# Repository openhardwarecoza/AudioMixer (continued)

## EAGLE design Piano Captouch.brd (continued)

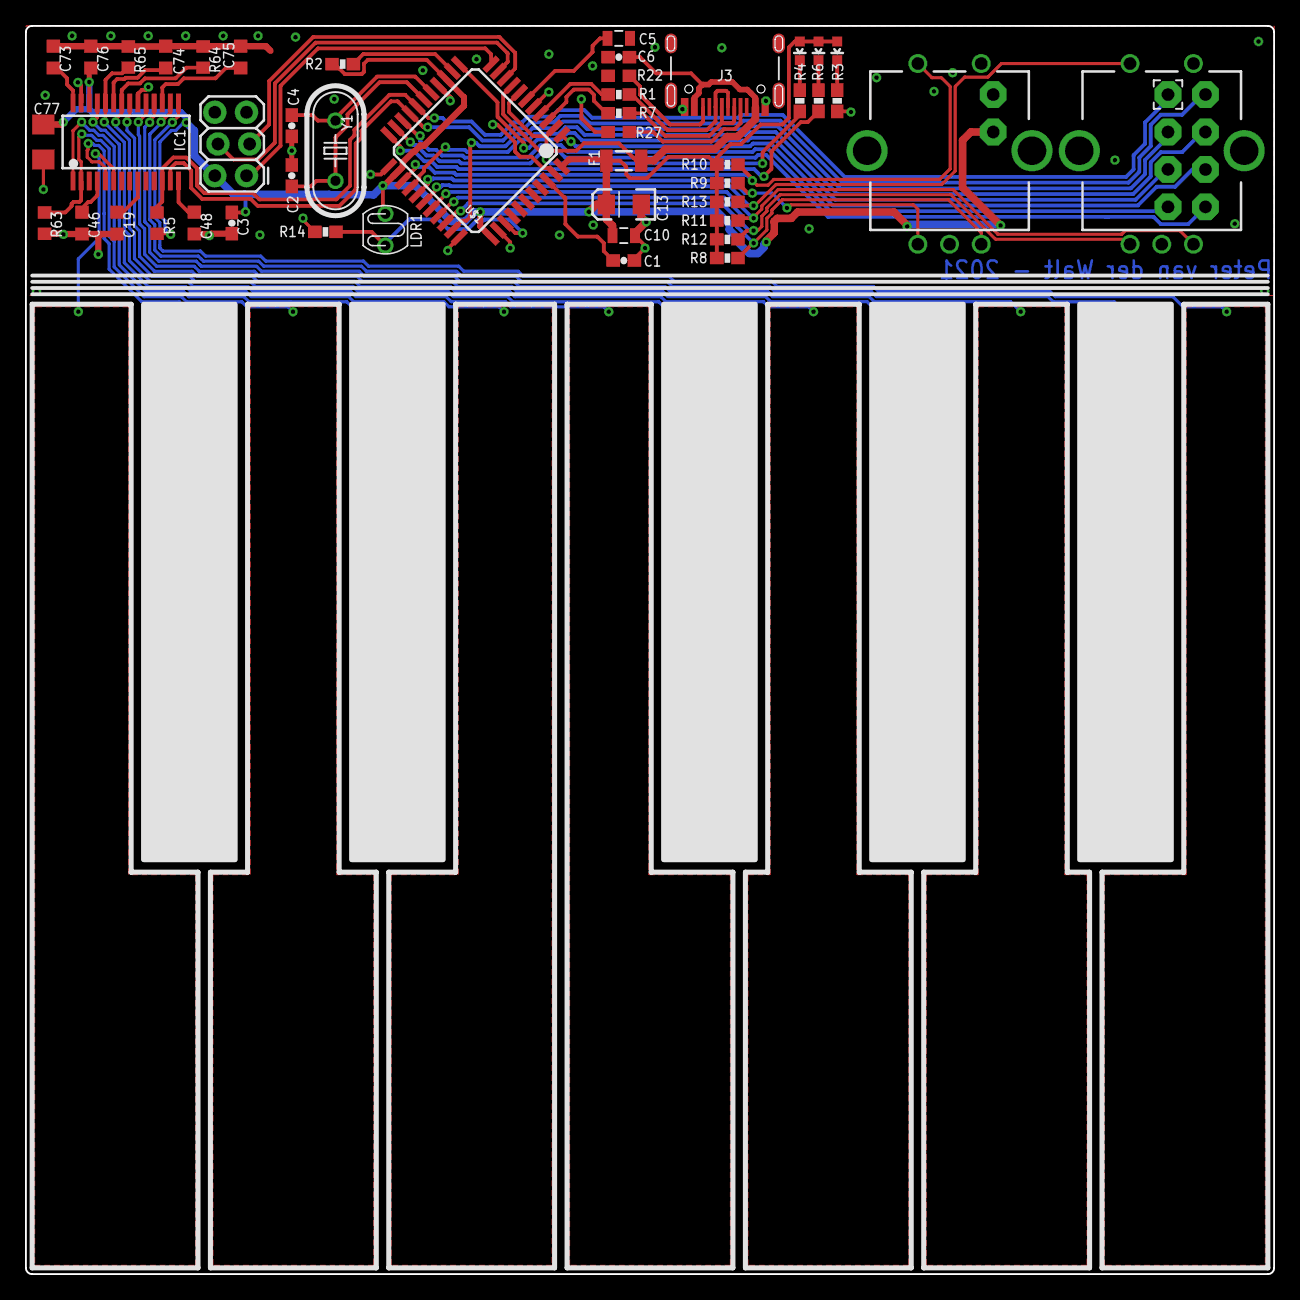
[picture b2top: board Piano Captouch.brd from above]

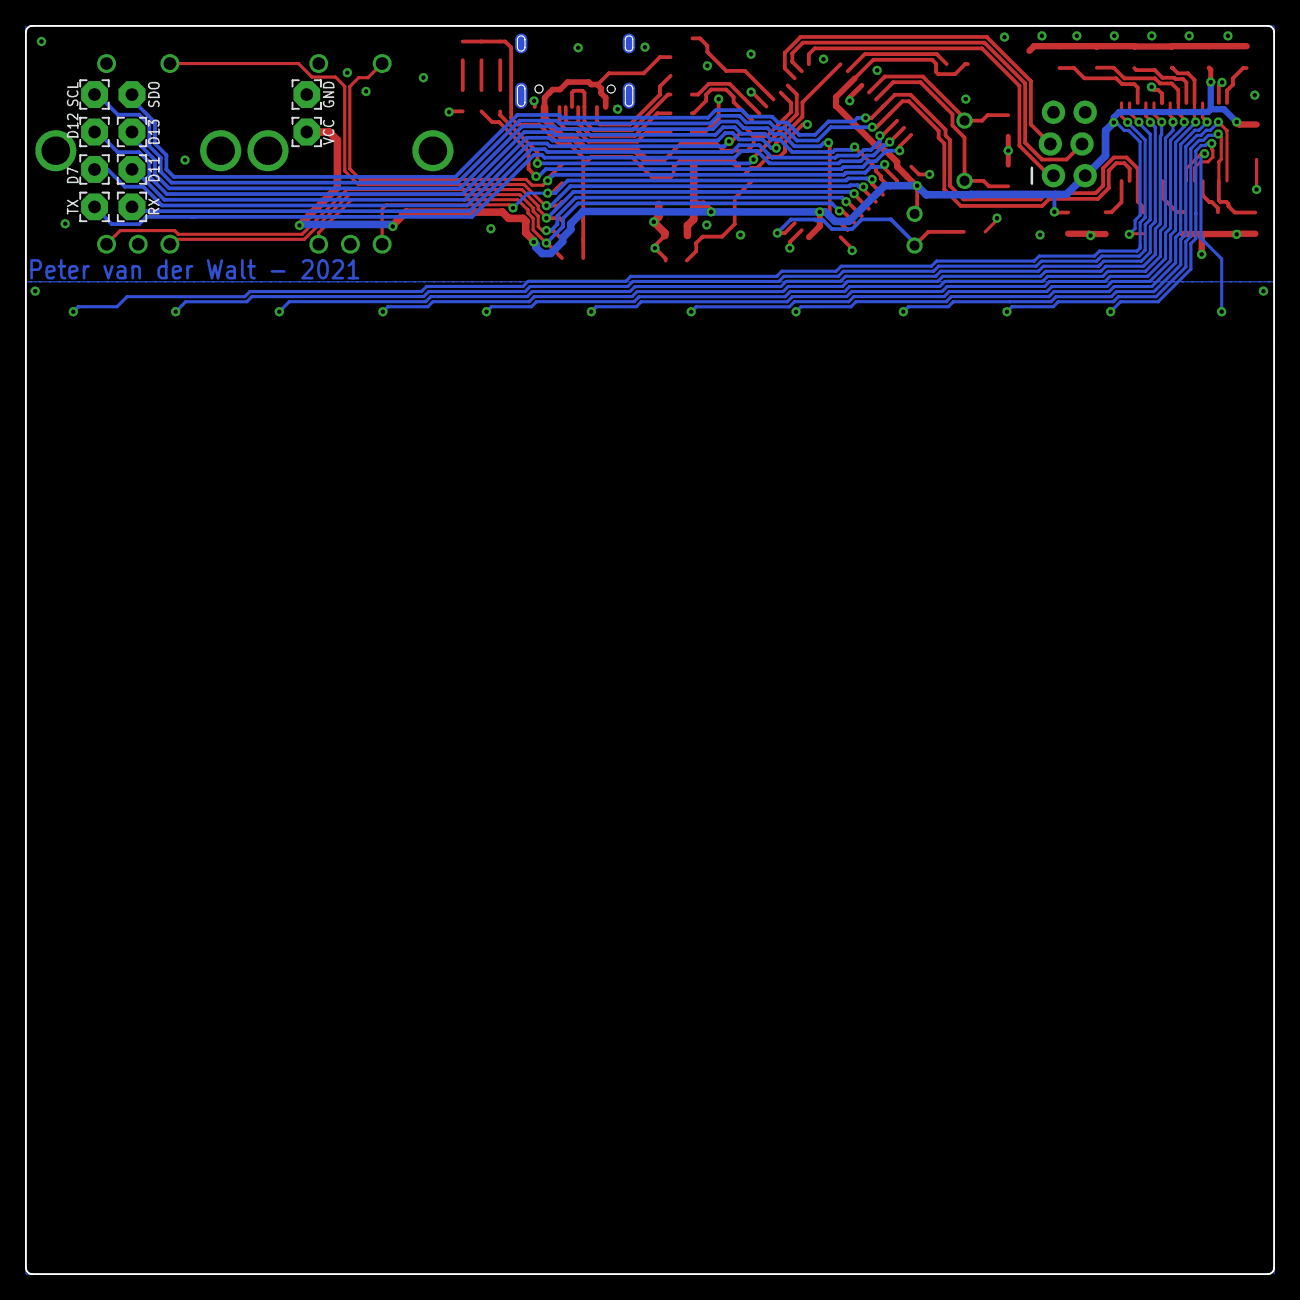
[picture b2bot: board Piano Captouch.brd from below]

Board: 2 copper layers, 100.0 x 100.0 mm, 57 parts (9 on the bottom side), 47 nets.

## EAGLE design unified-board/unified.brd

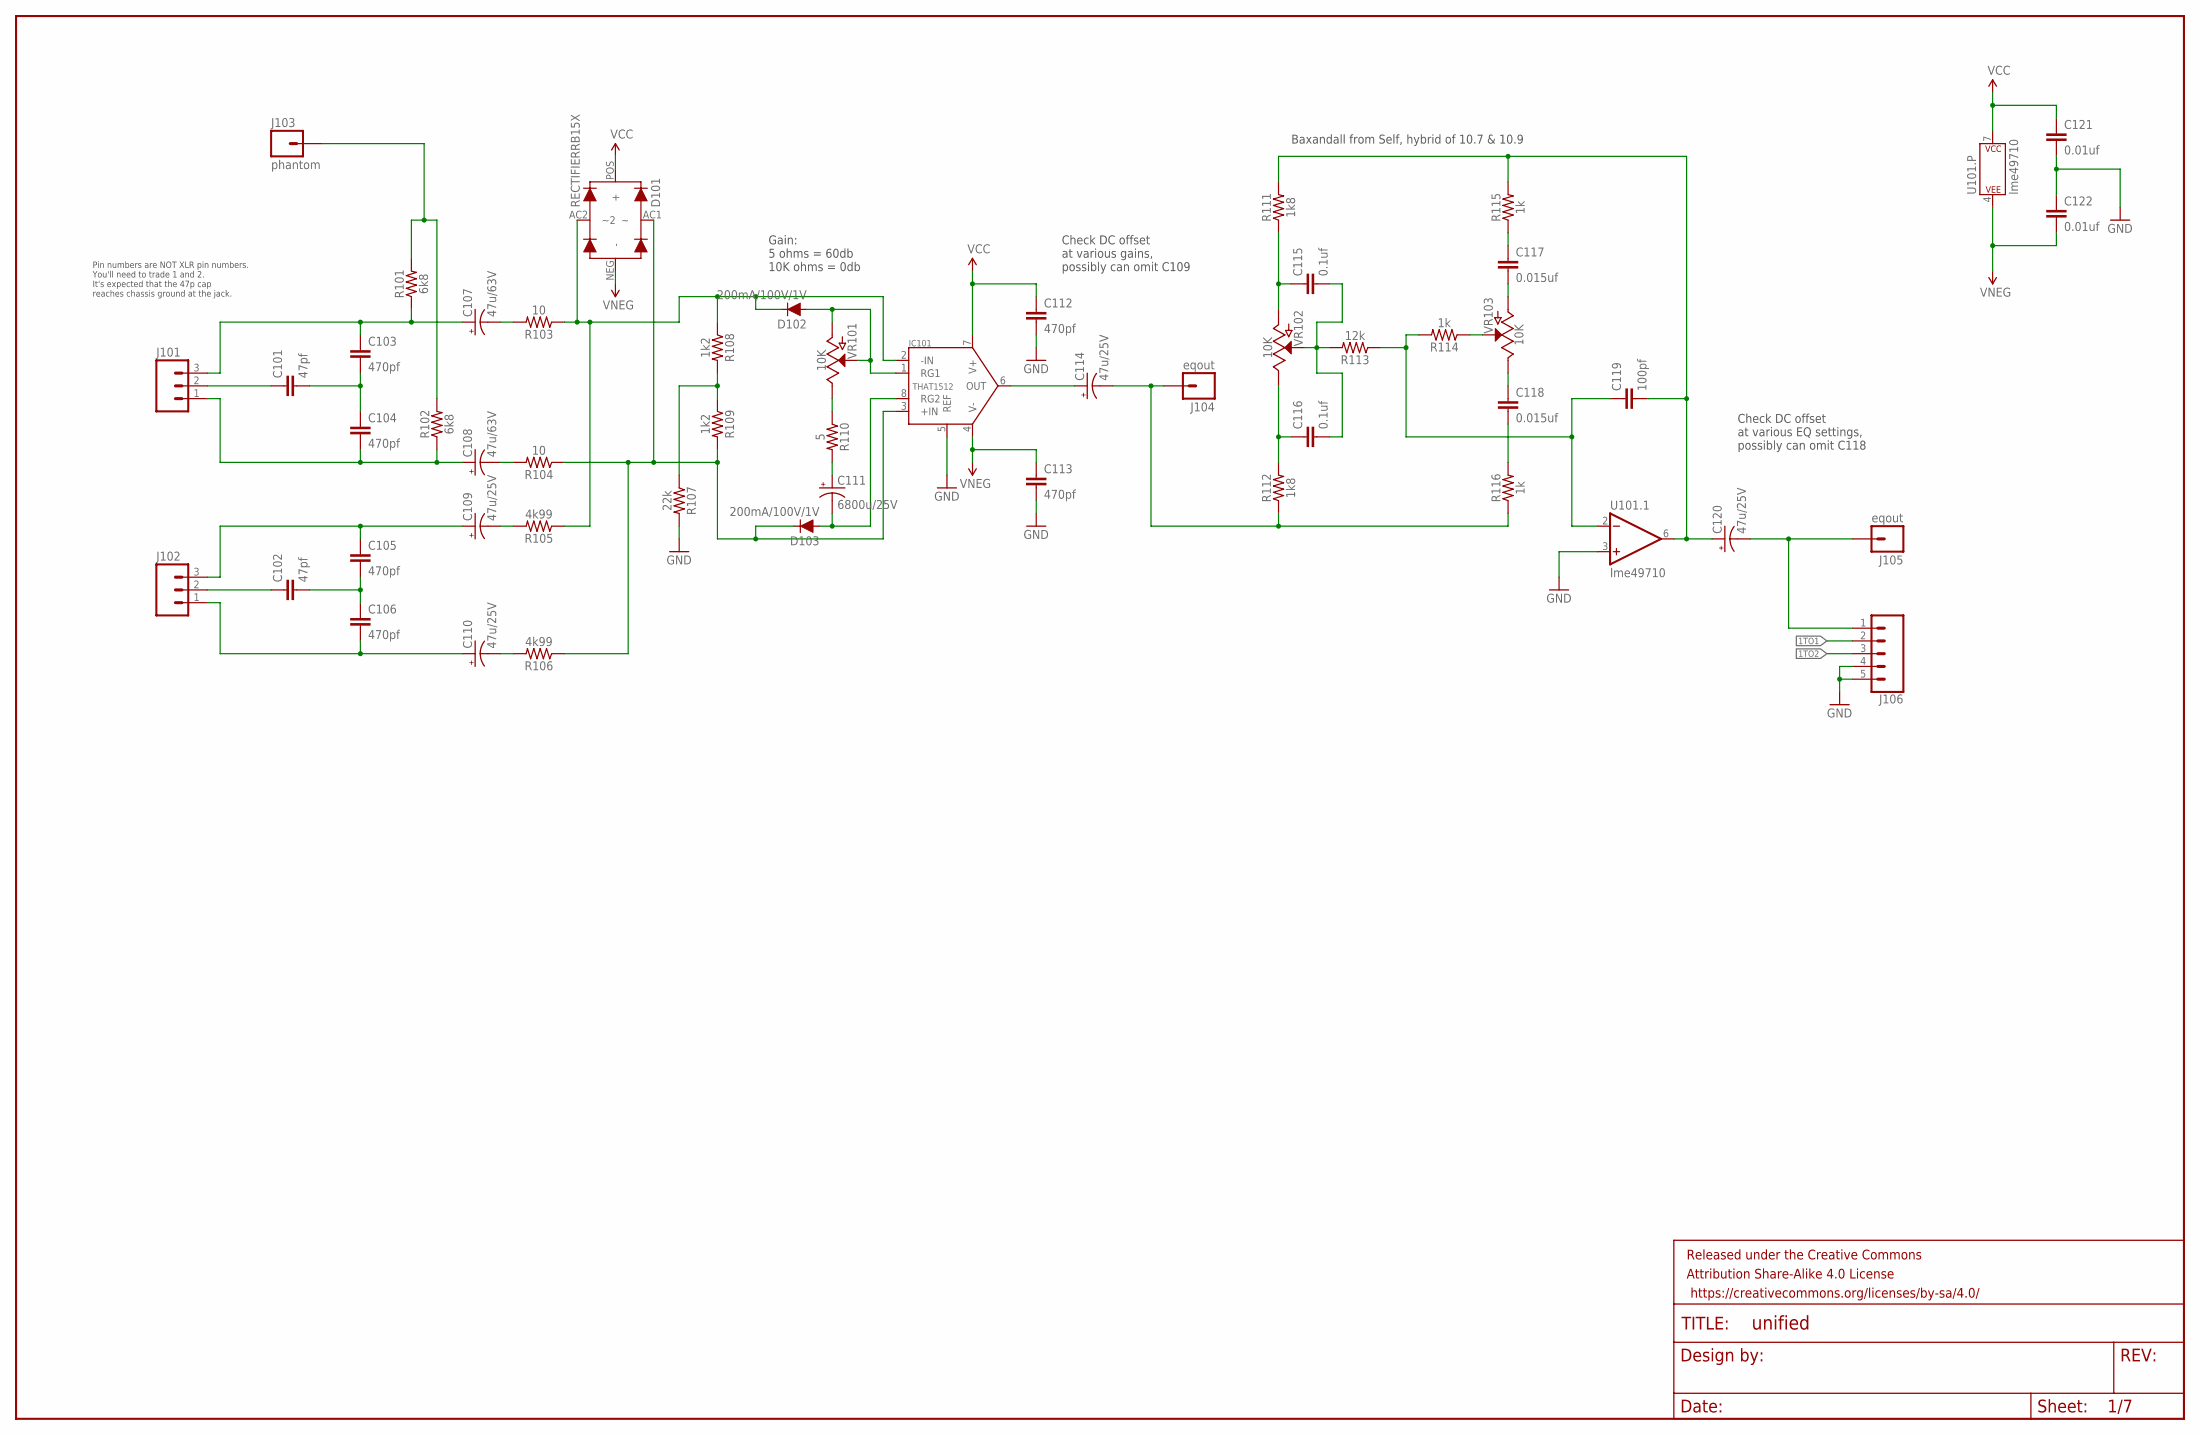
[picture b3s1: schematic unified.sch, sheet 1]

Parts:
C101, C102: 47pf; CAP-KEMET-GM-2.54LS
C103, C104, C105, C106, C112, C113: 470pf; CAP-KEMET-GM-2.54LS
C107, C108: 47u/63V; CAP-PANA-2LS-6DIAM
C109, C110, C114, C120: 47u/25V; CAP-PANA-2LS-5DIAM
C111: 6800u/25V; CAP-PANA-5LS-12.5DIAM
C115, C116: 0.1uf; WIMA-MKS2-2.5X7.2
C117, C118: 0.015uf; WIMA-MKS2-2.5X7.2
C119: 100pf; CAP-KEMET-GM-2.54LS
C121, C122: 0.01uf; WIMA-MKS2-2.5X7.2
D101: RECTIFIERRB15X; SM-RECTIFIER
D102, D103: 200mA/100V/1V; DIODE-1N4148
FRAME101: FRAME-LEDGER; CREATIVE_COMMONS
IC101: THAT1512; DIP08-KIT
J101, J102: M031X03_NO_SILK; 1X03_NO_SILK@1
J103: phantom; 1X01NS-KIT
J104, J105: eqout; 1X01NS-KIT
J106: CONN_05PTH_LONGPADS; 1X05_LONGPADS
R101, R102: 6k8; AXIAL-0.3
R103, R104: 10; AXIAL-0.3
R105, R106: 4k99; AXIAL-0.3
R107: 22k; AXIAL-0.3
R108, R109: 1k2; AXIAL-0.3
R110: 5; AXIAL-0.3
R111, R112: 1k8; AXIAL-0.3
R113: 12k; AXIAL-0.3
R114, R115, R116: 1k; AXIAL-0.3
U101: lme49710; DIP08-KIT
VR101: 10K; ROT-SW-POT
VR102, VR103: 10K; ALPHA-RV24AF40-POT

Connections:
1TO1: J106.2; also elsewhere on the board
1TO2: J106.3; also elsewhere on the board
EQ1OUT: C120.NEG (-), J105.1, J106.1
GND: C112.P$2 (2), C113.P$2 (2), C121.P$2 (2), C122.P$1 (1), IC101.5 (REF), J106.4, J106.5, R107.P$2 (2), U101.3 (+IN); also elsewhere on the board
L1+: C106.P$2 (2), C110.POS (+), J102.1
L1-: C105.P$1 (1), C109.POS (+), J102.3
L1GND: C102.P$1 (1), J102.2
M1+: C104.P$2 (2), C108.POS (+), J101.1, R102.P$1 (1)
M1-: C103.P$1 (1), C107.POS (+), J101.3, R101.P$1 (1)
M1GND: C101.P$1 (1), J101.2
unnamed: C115.P$1 (1), R111.P$1 (1), VR102.CCW (A)
unnamed: C116.P$1 (1), R112.P$2 (2), VR102.CW (E)
unnamed: C119.P$1 (1), R113.P$1 (1), R114.P$2 (2), U101.2 (-IN)
unnamed: C118.P$2 (2), R116.P$2 (2)
unnamed: C119.P$2 (2), C120.POS (+), R111.P$2 (2), R115.P$2 (2), U101.6 (OUT)
unnamed: R114.P$1 (1), VR103.WIP (S)
unnamed: C118.P$1 (1), VR103.CW (E)
unnamed: C115.P$2 (2), C116.P$2 (2), R113.P$2 (2), VR102.WIP (S)
unnamed: C117.P$2 (2), VR103.CCW (A)
unnamed: C117.P$1 (1), R115.P$1 (1)
unnamed: C111.NEG (-), D103.A, IC101.8 (RG2)
unnamed: C114.POS (+), IC101.6 (OUT)
unnamed: C101.P$2 (2), C103.P$2 (2), C104.P$1 (1)
unnamed: C108.NEG (-), R104.P$2 (2)
unnamed: J103.1, R101.P$2 (2), R102.P$2 (2)
unnamed: C107.NEG (-), R103.P$2 (2)
unnamed: D101.AC2 (~2), D102.C, IC101.2 (-IN), R103.P$1 (1), R105.P$1 (1), R108.P$1 (1)
unnamed: D101.AC1, D103.C, IC101.3 (+IN), R104.P$1 (1), R106.P$1 (1), R109.P$2 (2)
unnamed: R107.P$1 (1), R108.P$2 (2), R109.P$1 (1)
unnamed: D102.A, IC101.1 (RG1), VR101.CCW (A), VR101.WIP (S)
unnamed: R110.P$1 (1), VR101.CW (E)
unnamed: C111.POS (+), R110.P$2 (2)
unnamed: C102.P$2 (2), C105.P$2 (2), C106.P$1 (1)
unnamed: C110.NEG (-), R106.P$2 (2)
unnamed: C109.NEG (-), R105.P$2 (2)
PREOUT: C114.NEG (-), J104.1, R112.P$1 (1), R116.P$1 (1)
VCC: C112.P$1 (1), C121.P$1 (1), D101.POS (+), IC101.7 (V+), U101.7 (P$V+); also elsewhere on the board
VNEG: C113.P$1 (1), C122.P$2 (2), D101.NEG (-), IC101.4 (V-), U101.4 (P$V-); also elsewhere on the board

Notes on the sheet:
Pin numbers are NOT XLR pin numbers. You'll need to trade 1 and 2. It's expected that the 47p cap reaches chassis ground at the jack.
Baxandall from Self, hybrid of 10.7 & 10.9
Gain: 5 ohms = 60db 10K ohms = 0db
Check DC offset at various gains, possibly can omit C109
Check DC offset at various EQ settings, possibly can omit C118

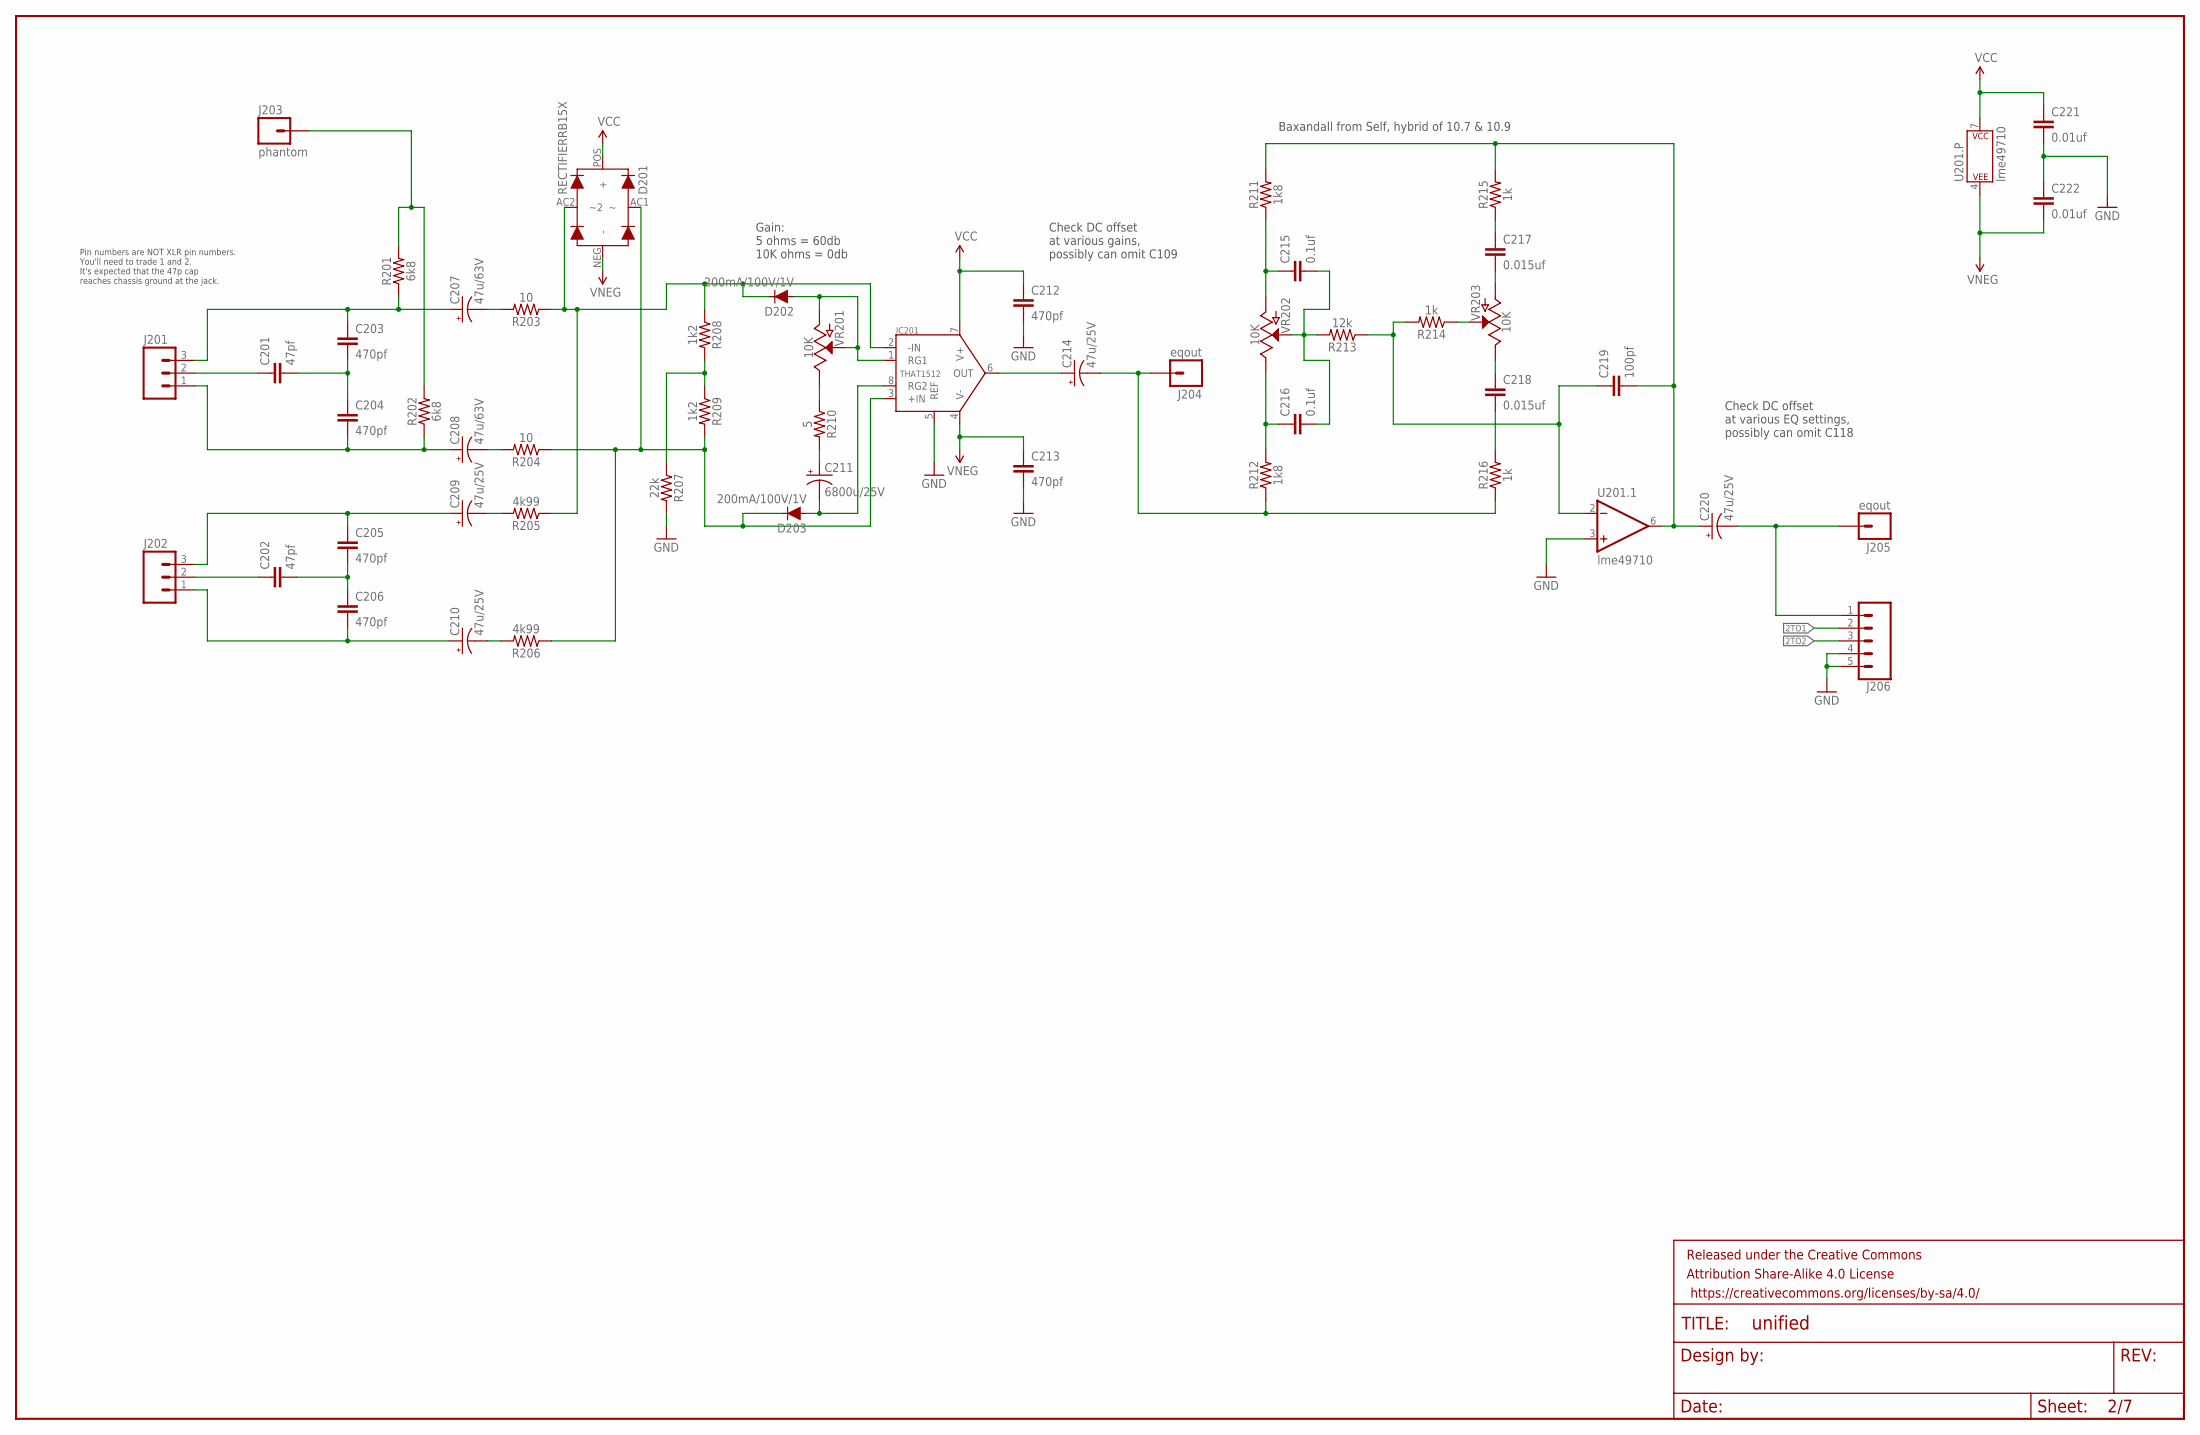
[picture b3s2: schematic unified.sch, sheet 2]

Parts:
C201, C202: 47pf; CAP-KEMET-GM-2.54LS
C203, C204, C205, C206, C212, C213: 470pf; CAP-KEMET-GM-2.54LS
C207, C208: 47u/63V; CAP-PANA-2LS-6DIAM
C209, C210, C214, C220: 47u/25V; CAP-PANA-2LS-5DIAM
C211: 6800u/25V; CAP-PANA-5LS-12.5DIAM
C215, C216: 0.1uf; WIMA-MKS2-2.5X7.2
C217, C218: 0.015uf; WIMA-MKS2-2.5X7.2
C219: 100pf; CAP-KEMET-GM-2.54LS
C221, C222: 0.01uf; WIMA-MKS2-2.5X7.2
D201: RECTIFIERRB15X; SM-RECTIFIER
D202, D203: 200mA/100V/1V; DIODE-1N4148
FRAME201: FRAME-LEDGER; CREATIVE_COMMONS
IC201: THAT1512; DIP08-KIT
J201, J202: M031X03_NO_SILK; 1X03_NO_SILK@1
J203: phantom; 1X01NS-KIT
J204, J205: eqout; 1X01NS-KIT
J206: CONN_05PTH_LONGPADS; 1X05_LONGPADS
R201, R202: 6k8; AXIAL-0.3
R203, R204: 10; AXIAL-0.3
R205, R206: 4k99; AXIAL-0.3
R207: 22k; AXIAL-0.3
R208, R209: 1k2; AXIAL-0.3
R210: 5; AXIAL-0.3
R211, R212: 1k8; AXIAL-0.3
R213: 12k; AXIAL-0.3
R214, R215, R216: 1k; AXIAL-0.3
U201: lme49710; DIP08-KIT
VR201: 10K; ROT-SW-POT
VR202, VR203: 10K; ALPHA-RV24AF40-POT

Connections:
2TO1: J206.2; also elsewhere on the board
2TO2: J206.3; also elsewhere on the board
EQ2OUT: C220.NEG (-), J205.1, J206.1
GND: C212.P$2 (2), C213.P$2 (2), C221.P$2 (2), C222.P$1 (1), IC201.5 (REF), J206.4, J206.5, R207.P$2 (2), U201.3 (+IN); also elsewhere on the board
unnamed: C214.NEG (-), J204.1, R212.P$1 (1), R216.P$1 (1)
unnamed: C215.P$1 (1), R211.P$1 (1), VR202.CCW (A)
unnamed: C216.P$1 (1), R212.P$2 (2), VR202.CW (E)
unnamed: R214.P$1 (1), VR203.WIP (S)
unnamed: C215.P$2 (2), C216.P$2 (2), R213.P$2 (2), VR202.WIP (S)
unnamed: C218.P$2 (2), R216.P$2 (2)
unnamed: C217.P$1 (1), R215.P$1 (1)
unnamed: C219.P$1 (1), R213.P$1 (1), R214.P$2 (2), U201.2 (-IN)
unnamed: C214.POS (+), IC201.6 (OUT)
unnamed: C201.P$1 (1), J201.2
unnamed: C201.P$2 (2), C203.P$2 (2), C204.P$1 (1)
unnamed: C203.P$1 (1), C207.POS (+), J201.3, R201.P$1 (1)
unnamed: C204.P$2 (2), C208.POS (+), J201.1, R202.P$1 (1)
unnamed: C208.NEG (-), R204.P$2 (2)
unnamed: J203.1, R201.P$2 (2), R202.P$2 (2)
unnamed: C207.NEG (-), R203.P$2 (2)
unnamed: R207.P$1 (1), R208.P$2 (2), R209.P$1 (1)
unnamed: C211.NEG (-), D203.A, IC201.8 (RG2)
unnamed: D202.A, IC201.1 (RG1), VR201.CCW (A), VR201.WIP (S)
unnamed: C218.P$1 (1), VR203.CW (E)
unnamed: C217.P$2 (2), VR203.CCW (A)
unnamed: R210.P$1 (1), VR201.CW (E)
unnamed: C211.POS (+), R210.P$2 (2)
unnamed: C202.P$1 (1), J202.2
unnamed: C202.P$2 (2), C205.P$2 (2), C206.P$1 (1)
unnamed: C205.P$1 (1), C209.POS (+), J202.3
unnamed: C206.P$2 (2), C210.POS (+), J202.1
unnamed: C210.NEG (-), R206.P$2 (2)
unnamed: C209.NEG (-), R205.P$2 (2)
unnamed: D201.AC2 (~2), D202.C, IC201.2 (-IN), R203.P$1 (1), R205.P$1 (1), R208.P$1 (1)
unnamed: D201.AC1, D203.C, IC201.3 (+IN), R204.P$1 (1), R206.P$1 (1), R209.P$2 (2)
unnamed: C219.P$2 (2), C220.POS (+), R211.P$2 (2), R215.P$2 (2), U201.6 (OUT)
VCC: C212.P$1 (1), C221.P$1 (1), D201.POS (+), IC201.7 (V+), U201.7 (P$V+); also elsewhere on the board
VNEG: C213.P$1 (1), C222.P$2 (2), D201.NEG (-), IC201.4 (V-), U201.4 (P$V-); also elsewhere on the board

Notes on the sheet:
Pin numbers are NOT XLR pin numbers. You'll need to trade 1 and 2. It's expected that the 47p cap reaches chassis ground at the jack.
Baxandall from Self, hybrid of 10.7 & 10.9
Gain: 5 ohms = 60db 10K ohms = 0db
Check DC offset at various gains, possibly can omit C109
Check DC offset at various EQ settings, possibly can omit C118

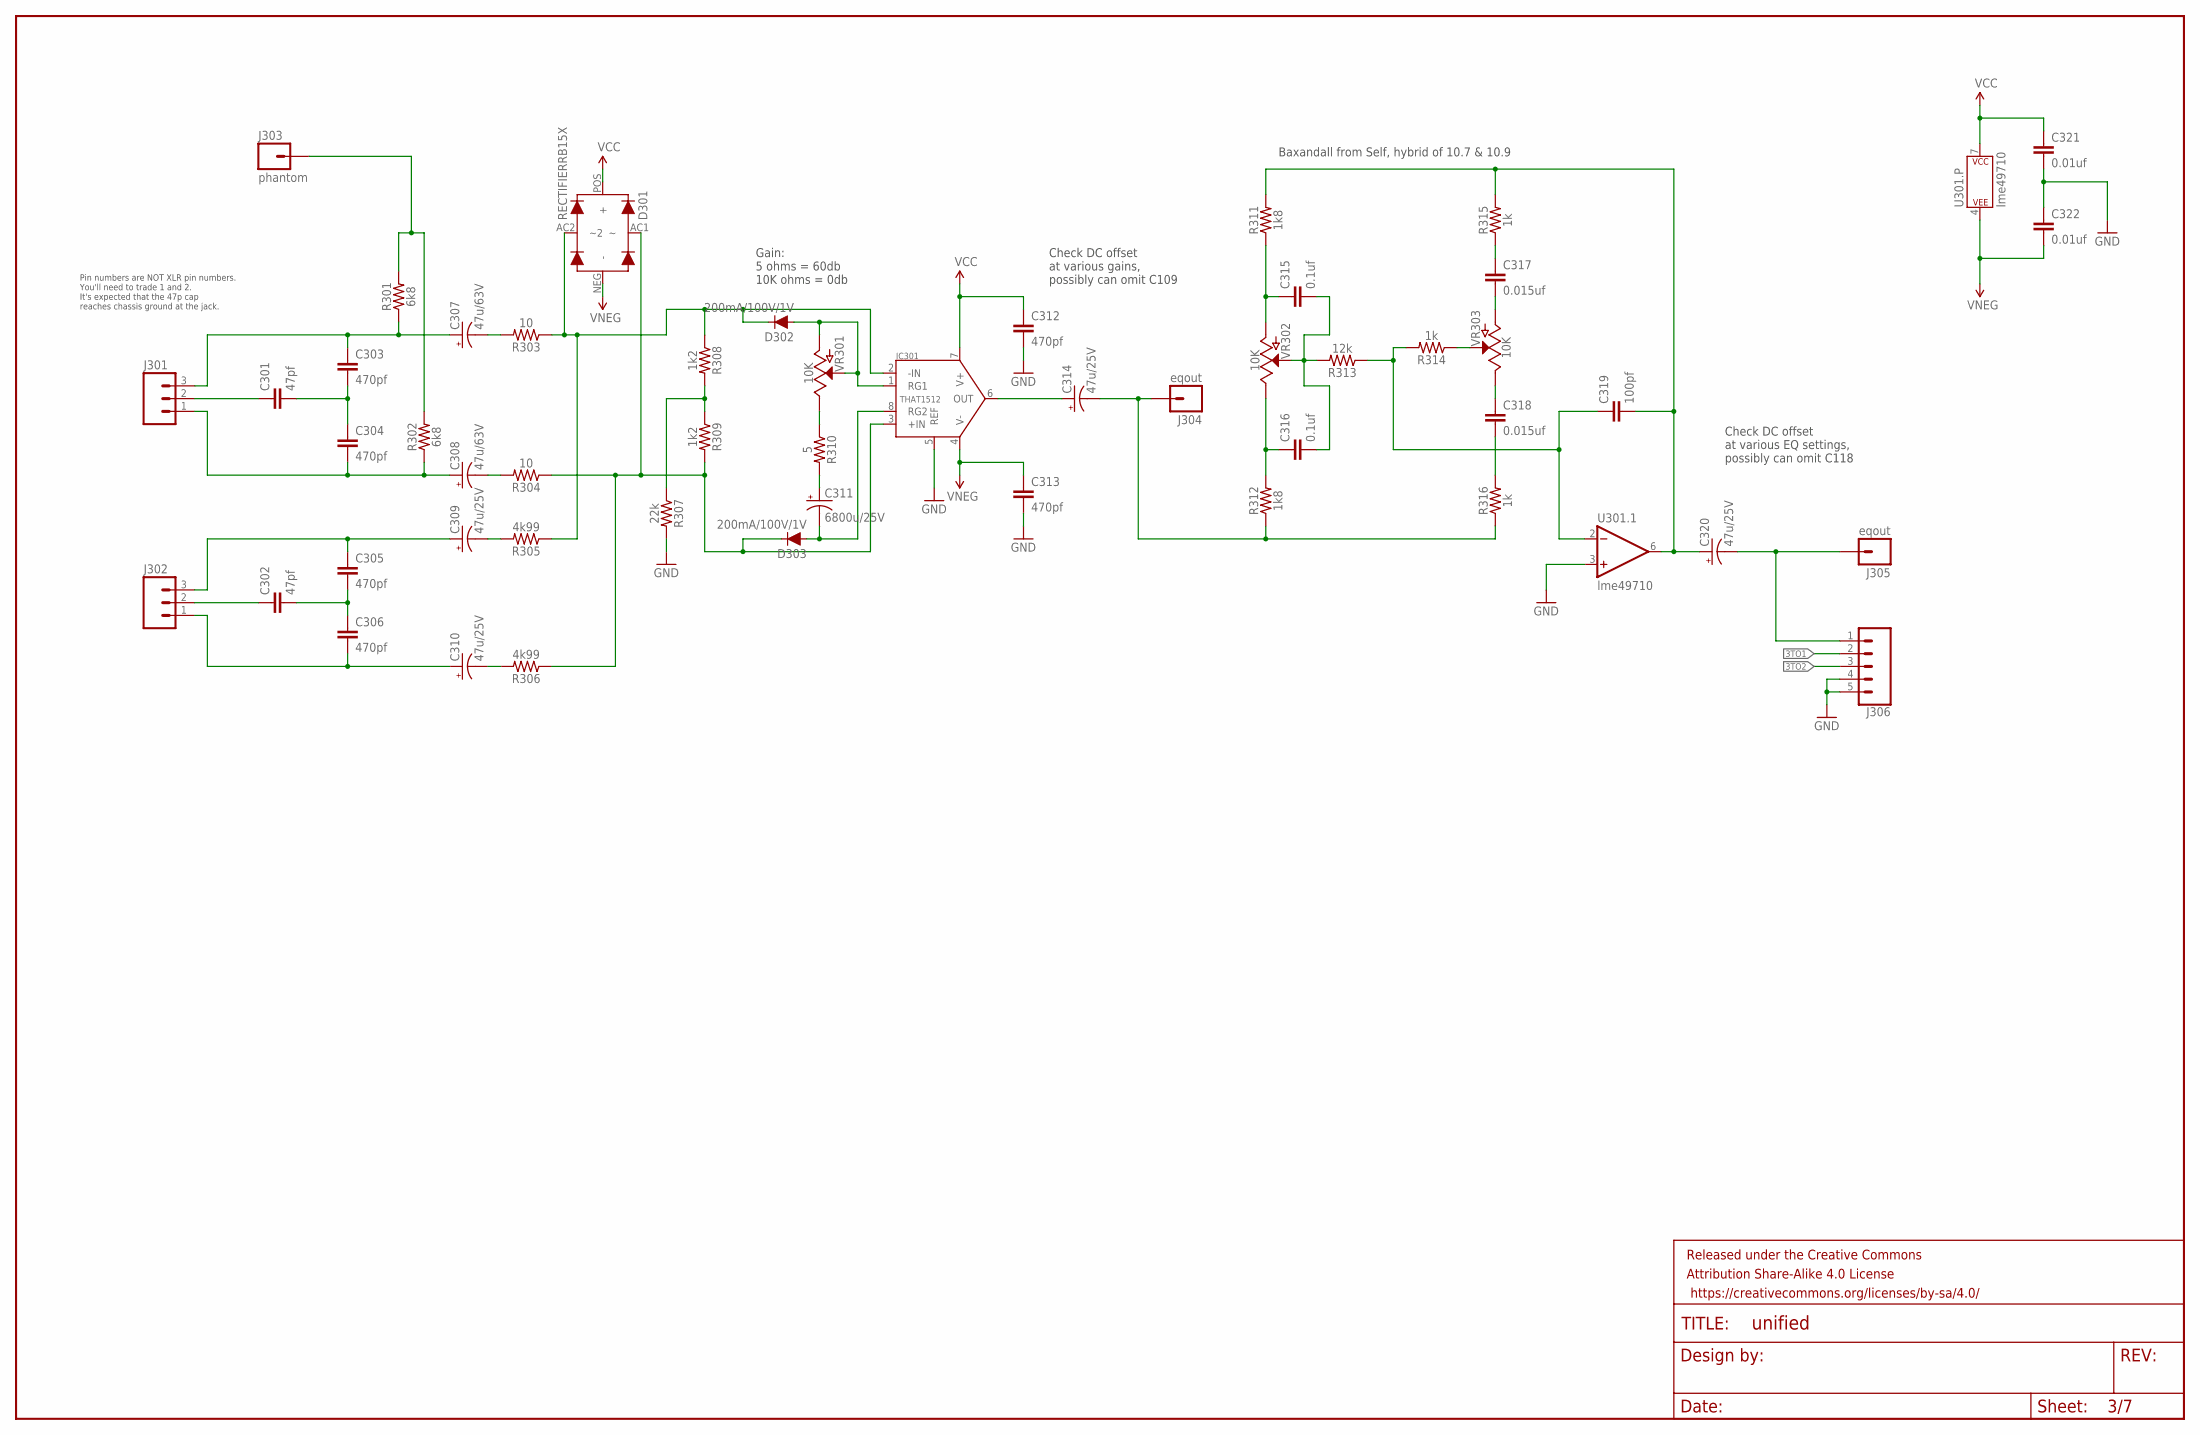
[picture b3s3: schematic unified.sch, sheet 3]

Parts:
C301, C302: 47pf; CAP-KEMET-GM-2.54LS
C303, C304, C305, C306, C312, C313: 470pf; CAP-KEMET-GM-2.54LS
C307, C308: 47u/63V; CAP-PANA-2LS-6DIAM
C309, C310, C314, C320: 47u/25V; CAP-PANA-2LS-5DIAM
C311: 6800u/25V; CAP-PANA-5LS-12.5DIAM
C315, C316: 0.1uf; WIMA-MKS2-2.5X7.2
C317, C318: 0.015uf; WIMA-MKS2-2.5X7.2
C319: 100pf; CAP-KEMET-GM-2.54LS
C321, C322: 0.01uf; WIMA-MKS2-2.5X7.2
D301: RECTIFIERRB15X; SM-RECTIFIER
D302, D303: 200mA/100V/1V; DIODE-1N4148
FRAME301: FRAME-LEDGER; CREATIVE_COMMONS
IC301: THAT1512; DIP08-KIT
J301, J302: M031X03_NO_SILK; 1X03_NO_SILK@1
J303: phantom; 1X01NS-KIT
J304, J305: eqout; 1X01NS-KIT
J306: CONN_05PTH_LONGPADS; 1X05_LONGPADS
R301, R302: 6k8; AXIAL-0.3
R303, R304: 10; AXIAL-0.3
R305, R306: 4k99; AXIAL-0.3
R307: 22k; AXIAL-0.3
R308, R309: 1k2; AXIAL-0.3
R310: 5; AXIAL-0.3
R311, R312: 1k8; AXIAL-0.3
R313: 12k; AXIAL-0.3
R314, R315, R316: 1k; AXIAL-0.3
U301: lme49710; DIP08-KIT
VR301: 10K; ROT-SW-POT
VR302, VR303: 10K; ALPHA-RV24AF40-POT

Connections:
3TO1: J306.2; also elsewhere on the board
3TO2: J306.3; also elsewhere on the board
EQ3OUT: C320.NEG (-), J305.1, J306.1
GND: C312.P$2 (2), C313.P$2 (2), C321.P$2 (2), C322.P$1 (1), IC301.5 (REF), J306.4, J306.5, R307.P$2 (2), U301.3 (+IN); also elsewhere on the board
unnamed: C314.NEG (-), J304.1, R312.P$1 (1), R316.P$1 (1)
unnamed: C315.P$1 (1), R311.P$1 (1), VR302.CCW (A)
unnamed: C316.P$1 (1), R312.P$2 (2), VR302.CW (E)
unnamed: R314.P$1 (1), VR303.WIP (S)
unnamed: C315.P$2 (2), C316.P$2 (2), R313.P$2 (2), VR302.WIP (S)
unnamed: C318.P$2 (2), R316.P$2 (2)
unnamed: C317.P$1 (1), R315.P$1 (1)
unnamed: C319.P$1 (1), R313.P$1 (1), R314.P$2 (2), U301.2 (-IN)
unnamed: C314.POS (+), IC301.6 (OUT)
unnamed: C301.P$1 (1), J301.2
unnamed: C301.P$2 (2), C303.P$2 (2), C304.P$1 (1)
unnamed: C303.P$1 (1), C307.POS (+), J301.3, R301.P$1 (1)
unnamed: C304.P$2 (2), C308.POS (+), J301.1, R302.P$1 (1)
unnamed: C308.NEG (-), R304.P$2 (2)
unnamed: J303.1, R301.P$2 (2), R302.P$2 (2)
unnamed: C307.NEG (-), R303.P$2 (2)
unnamed: R307.P$1 (1), R308.P$2 (2), R309.P$1 (1)
unnamed: C311.NEG (-), D303.A, IC301.8 (RG2)
unnamed: D302.A, IC301.1 (RG1), VR301.CCW (A), VR301.WIP (S)
unnamed: C318.P$1 (1), VR303.CW (E)
unnamed: C317.P$2 (2), VR303.CCW (A)
unnamed: R310.P$1 (1), VR301.CW (E)
unnamed: C311.POS (+), R310.P$2 (2)
unnamed: C302.P$1 (1), J302.2
unnamed: C302.P$2 (2), C305.P$2 (2), C306.P$1 (1)
unnamed: C305.P$1 (1), C309.POS (+), J302.3
unnamed: C306.P$2 (2), C310.POS (+), J302.1
unnamed: C310.NEG (-), R306.P$2 (2)
unnamed: C309.NEG (-), R305.P$2 (2)
unnamed: D301.AC2 (~2), D302.C, IC301.2 (-IN), R303.P$1 (1), R305.P$1 (1), R308.P$1 (1)
unnamed: D301.AC1, D303.C, IC301.3 (+IN), R304.P$1 (1), R306.P$1 (1), R309.P$2 (2)
unnamed: C319.P$2 (2), C320.POS (+), R311.P$2 (2), R315.P$2 (2), U301.6 (OUT)
VCC: C312.P$1 (1), C321.P$1 (1), D301.POS (+), IC301.7 (V+), U301.7 (P$V+); also elsewhere on the board
VNEG: C313.P$1 (1), C322.P$2 (2), D301.NEG (-), IC301.4 (V-), U301.4 (P$V-); also elsewhere on the board

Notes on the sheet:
Pin numbers are NOT XLR pin numbers. You'll need to trade 1 and 2. It's expected that the 47p cap reaches chassis ground at the jack.
Baxandall from Self, hybrid of 10.7 & 10.9
Gain: 5 ohms = 60db 10K ohms = 0db
Check DC offset at various gains, possibly can omit C109
Check DC offset at various EQ settings, possibly can omit C118
